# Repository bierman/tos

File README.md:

# TOS Board Connection Map (v1.1)

## Raspberry Pi Connecter
| Raspberry Pi Physical Pin   | GPIO Pin              | TOS Connection                                                | Description             |
|-----------------------------|-----------------------|---------------------------------------------------------------|-------------------------|
| 1                           | 3.3v                  | 3.3v line (jumpered with pi pin 1)                            | 3.3v                    |
| 2                           | 5v                    | 5v line (jumpered with pin 4)                                 | 5v                      |
| 3                           | GPIO 2 / SDA1         | Red LED through R1 (330 Ohm)                                  | LED Red                 |
| 4                           | 5v                    | 5v line (jumpered with pin 2)                                 | 5v                      |
| 5                           | GPIO 3 / SCL1         | NC                                                            | NC                      |
| 6                           | GND                   | GND (all grounds jumpered)                                    | Ground                  |
| 7                           | GPIO 4                | NC                                                            | NC                      |
| 8                           | GPIO 14 / TXD         | MAX232 Pin 11                                                 | TX TTL                  |
| 9                           | GND                   | GND (all grounds jumpered)                                    | Ground                  |
| 10                          | GPIO 15 / RXD         | MAX232 Pin 12                                                 | RX TTL                  |
| 11                          | GPIO 17               | Blue LED through R3 (220 Ohm)                                 | LED Blue                |
| 12                          | GPIO 18               | NC                                                            | NC                      |
| 13                          | GPIO 27               | Green LED through R2 (220 Ohm)                                | LED Green               |
| 14                          | GND                   | GND (all grounds jumpered)                                    | Ground                  |
| 15                          | GPIO 22               | SW1 - Pull up to 3.3v through R6 (4.7K Ohm)                   | Button                  |
| 16                          | GPIO 23               | Keyboard pin 5                                                | PS2 Keyboard CLK        |
| 17                          | 3.3v                  | 3.3v line (jumpered with pi pin 17)                           | 3.3v                    |
| 18                          | GPIO 24               | Keyboard Pin 1                                                | PS2 Keyboard Data       |
| 19                          | GPIO 10 / MOSI        | PMOD pin 2                                                    | PMOD 2 MOSI             |
| 20                          | GND                   | GND (all grounds jumpered)                                    | Ground                  |
| 21                          | GPIO 9 / MISO         | PMOD pin 3                                                    | PMOD 3 MISO             |
| 22                          | GPIO 25               | NC                                                            | NC                      |
| 23                          | GPIO 11 / SCLK        | PMOD pin 4                                                    | PMOD 4 SCK              |
| 24                          | GPIO 8 / CE0          | PMOD pin 1                                                    | PMOD 1 CS               |
| 25                          | GND                   | GND (all grounds jumpered)                                    | Ground                  |
| 26                          | GPIO 7 / CE1          | NC                                                            | NC                      |
| 27                          | GPIO 0 / ID_SD (SDA0) | Mouse Pin 1                                                   | PS2 Mouse Data          |
| 28                          | GPIO 1 / ID_SC (SCL0) | Mouse Pin 5                                                   | PS2 Mouse CLK           |
| 29                          | GPIO 5                | NC                                                            | NC                      |
| 30                          | GND                   | GND (all grounds jumpered)                                    | Ground                  |
| 31                          | GPIO 6                | NC                                                            | NC                      |
| 32                          | GPIO 12 / PWM0        | PMOD pin 7                                                    | PMOD7 - Int             |
| 33                          | GPIO 13 / PWM1        | NC                                                            | NC                      |
| 34                          | GND                   | GND (all grounds jumpered)                                    | Ground                  |
| 35                          | GPIO 19               | NC                                                            | NC                      |
| 36                          | GPIO 16               | PDOD pin 8                                                    | PMOD8 - Reset           |
| 37                          | GPIO 26               | NC                                                            | NC                      |
| 38                          | GPIO 20 / PCM_DIN     | PMOD pin 9                                                    | PMOD9                   |
| 39                          | GND                   | GND (all grounds jumpered)                                    | Ground                  |
| 40                          | GPIO 21 / PCM_DOUT    | PMOD pin 10                                                   | PMOD10                  |

## RS-232 Connecter

| RS-232 Connector            | GPIO Pin              | TOS Connection                                                | Description             |
|-----------------------------|-----------------------|---------------------------------------------------------------|-------------------------|
| 1                           |                       | NC                                                            | NC                      |
| 2                           |                       | MAX232 Pin 13                                                 | RX                      |
| 3                           |                       | MAX232 Pin 14                                                 | TX                      |
| 4                           |                       | NC                                                            | NC                      |
| 5                           |                       | GND                                                           | Ground                  |
| 6                           |                       | NC                                                            | NC                      |
| 7                           |                       | Jumpered to RS232 Pin 8                                       | Jumpered to RS232 Pin 8 |
| 8                           |                       | Jumpered to RS232 Pin 7                                       | Jumpered to RS232 Pin 7 |
| 9                           |                       | NC                                                            | NC                      |

## MAX232 chip

| MAX232                      | GPIO Pin              | TOS Connection                                                | Description             |
|-----------------------------|-----------------------|---------------------------------------------------------------|-------------------------|
| 1                           |                       | C1+ (0.1uf) to MAX232 pin 3                                   |                         |
| 2                           |                       | C4+ (0.1uf) to GND                                            |                         |
| 3                           |                       | C1- (0.1uf) to MAX232 pin 1                                   |                         |
| 4                           |                       | C2+ (0.1uf) to MAX232 pin 5                                   |                         |
| 5                           |                       | C2- (0.1uf) to MAX232 pin 4                                   |                         |
| 6                           |                       | C3- (0.1uf) to GND                                            |                         |
| 7                           |                       | NC                                                            | NC                      |
| 8                           |                       | NC                                                            | NC                      |
| 9                           |                       | NC                                                            | NC                      |
| 10                          |                       | GND                                                           | Ground                  |
| 11                          |                       | PI Physical pin 8                                             | TXTTL                   |
| 12                          |                       | Pi Physical Pin 10                                            | RXTTL                   |
| 13                          |                       | RS232 Pin 2                                                   | RX                      |
| 14                          |                       | RS232 Pin 3                                                   | TX                      |
| 15                          |                       | GND                                                           | Ground                  |
| 16                          |                       | 3.3v                                                          | 3.3v                    |

## PMOD Connecter

| PMOD                        | GPIO Pin              | TOS Connection                                                | Description             |
|-----------------------------|-----------------------|---------------------------------------------------------------|-------------------------|
| 1                           | GPIO 8 / CE0          | Pi Physical Pin 24                                            | PMOD 1 - CS             |
| 2                           | GPIO 10 / MOSI        | Pi Physical Pin 19                                            | PMOD 2 - MOSI           |
| 3                           | GPIO 9 / MISO         | Pi Physical Pin 21                                            | PMOD 3  - MISO          |
| 4                           | GPIO 11 / SCLK        | Pi Physical Pin 23                                            | PMOD 4 - SClock         |
| 5                           |                       | GND                                                           | Ground                  |
| 6                           |                       | 3.3v                                                          | 3.3v                    |
| 7                           | GPIO 12 / PWM0        | Pi Physical Pin 32                                            | PMOD 7 - INT            |
| 8                           | GPIO 16               | Pi Physical Pin 36                                            | PMOD 8 - RESET          |
| 9                           | GPIO 20 / PCM_DIN     | Pi Physical Pin 38                                            | PMOD 9                  |
| 10                          | GPIO 21 / PCM_DOUT    | Pi Physical Pin 40                                            | PMOD 10                 |
| 11                          |                       | GND                                                           | Ground                  |
| 12                          |                       | 3.3v                                                          | 3.3v                    |

## PS2 Mouse Connecter

| PS2 Mouse                   | GPIO Pin              | TOS Connection                                                | Description             |
|-----------------------------|-----------------------|---------------------------------------------------------------|-------------------------|
| 1                           | GPIO 0 / ID_SD (SDA0) | Pi Physical Pin 27 (pull up to 3.3v through R8 (2K Ohm)       | PS2 Mouse Data          |
| 2                           |                       | NC                                                            | NC                      |
| 3                           |                       | GND                                                           | Ground                  |
| 4                           |                       | 5v                                                            | 5v                      |
| 5                           | GPIO 1 / ID_SC (SCL0) | Pi Physical Pin 28 (pull up to 3.3v through R7 (2K Ohm)       | PS2 Mouse Clock         |
| 6                           |                       | NC                                                            | NC                      |

## PS2 Keyboard Connecter

| PS2 Keyboard                | GPIO Pin              | TOS Connection                                                | Description             |
|-----------------------------|-----------------------|---------------------------------------------------------------|-------------------------|
| 1                           | GPIO 24               | Pi Physical Pin 18 (pull up to 3.3v through R5 (2K Ohm)       | PS2 Keyboard Data       |
| 2                           |                       | NC                                                            | NC                      |
| 3                           |                       | GND                                                           | Ground                  |
| 4                           |                       | 5v                                                            | 5v                      |
| 5                           | GPIO 23               | Pi Physical Pin 16 (pull up to 3.3v through R4 (2K Ohm)       | PS2 Keyboard Clock      |
| 6                           |                       | NC                                                            | NC                      |

## Breakout Connecter

| Breakout                    | GPIO Pin              | TOS Connection                                                | Description             |
|-----------------------------|-----------------------|---------------------------------------------------------------|-------------------------|
| 1                           |                       | GND                                                           | Ground                  |
| 2                           | GPIO 22               | Pi Physical 15  / SW1 - Pull up to 3.3v through R6 (4.7K Ohm) | Button                  |
| 3                           | GPIO 2 / SDA1         | Pi Physical Pin 3                                             | Red LED                 |
| 4                           | GPIO 24               | Pi Physical Pin 18 / PS2 Keyboard pin 1                       | PS2 Keyboar Data        |
| 5                           | GPIO 23               | Pi Physical Pin 16 / PS2 Keyboard pin 5                       | PS2 Keyboard Clock      |
| 6                           |                       | RS-232 pin 4                                                  | RX                      |
| 7                           |                       | RS-232 pin 3                                                  | TX                      |

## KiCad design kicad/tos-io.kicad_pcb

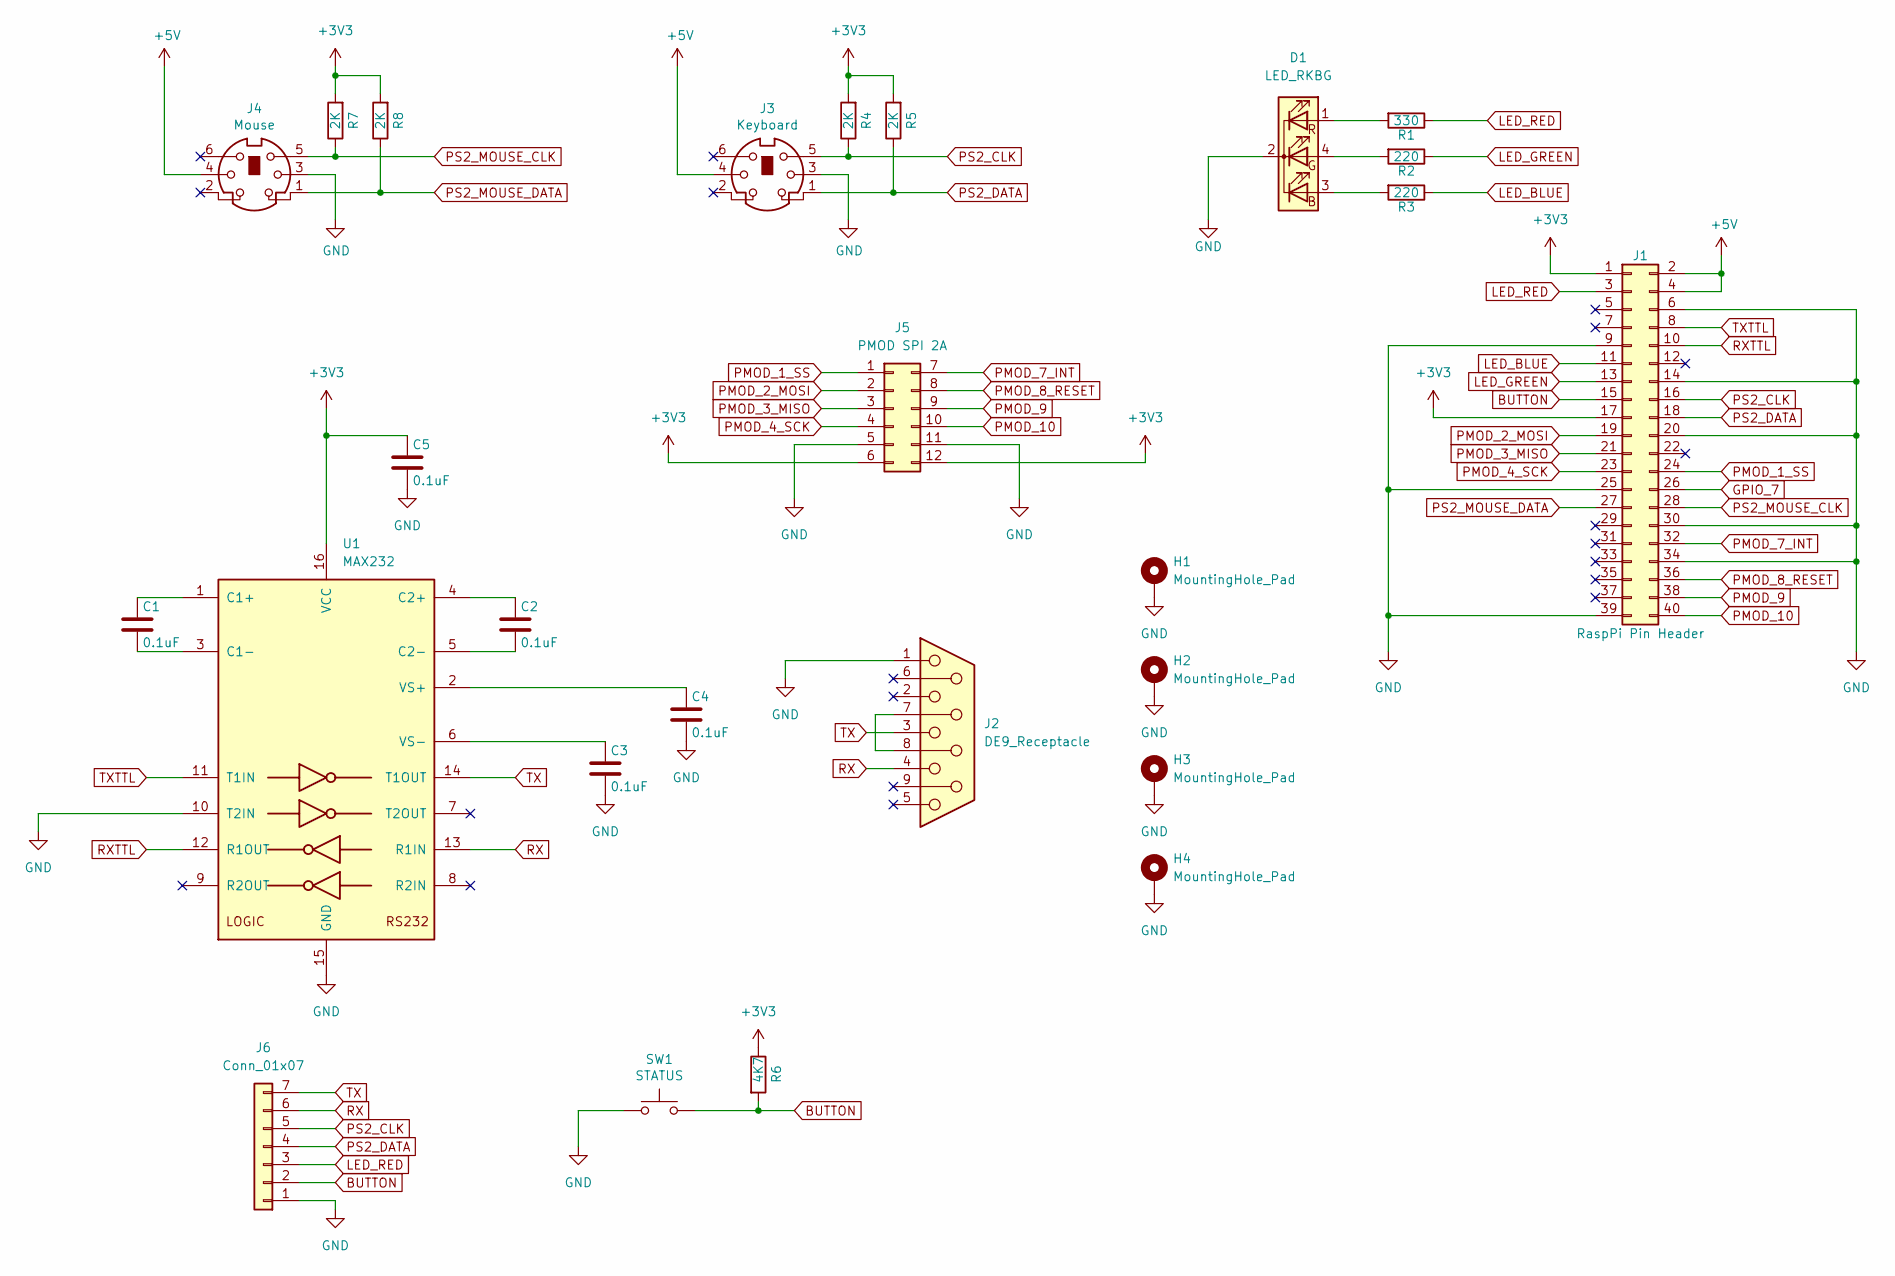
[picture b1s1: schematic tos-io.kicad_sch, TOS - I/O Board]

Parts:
C1, C2, C3, C4, C5: 0.1uF; C_0805_2012Metric_Pad1.18x1.45mm_HandSolder; LCSC C49678
D1: LED_RKBG; LED_D5.0mm-4_RGB
H1, H2, H3, H4: MountingHole_Pad; MountingHole_3mm_Pad_Via
J1: RaspPi Pin Header; PinHeader_2x20_P2.54mm_Vertical; LCSC C132439
J2: DE9_Receptacle; DSUB-9_Female_Horizontal_P2.77x2.84mm_EdgePinOffset7.70mm_H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
J3: Keyboard; minidin_6_ps2_pcb_mount; LCSC C77848
J4: Mouse; minidin_6_ps2_pcb_mount
J5: PMOD SPI 2A; PinSocket_2x06_Top_Bottom_P2.54mm_Vertical; LCSC C358728
J6: Conn_01x07; PinHeader_1x07_P2.54mm_Vertical; LCSC C5360900
R1: 330; R_0805_2012Metric_Pad1.20x1.40mm_HandSolder
R2, R3: 220; R_0805_2012Metric_Pad1.20x1.40mm_HandSolder
R4, R5, R7, R8: 2K; R_0805_2012Metric_Pad1.20x1.40mm_HandSolder
R6: 4K7; R_0805_2012Metric_Pad1.20x1.40mm_HandSolder
SW1: STATUS; SW_PUSH_6mm; LCSC C722960
U1: MAX232; TSSOP-16_4.4x5mm_P0.65mm; LCSC C406863

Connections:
+3V3: C5.1, J1.1, J1.17, J5.6, J5.12, R4.2, R5.2, R6.1, R7.2, R8.2, U1.16 (VCC)
+5V: J1.2, J1.4, J3.4, J4.4
BUTTON: J1.15, J6.2, R6.2, SW1.2
GND: C3.2, C4.2, C5.2, D1.2 (K), H1.1, H2.1, H3.1, H4.1, J1.6, J1.9, J1.14, J1.20, J1.25, J1.30, J1.34, J1.39, J2.1, J3.3, J4.3, J5.5, J5.11, J6.1, SW1.1, U1.10 (T2IN), U1.15 (GND)
GPIO_7: J1.26
LED_BLUE: J1.11, R3.1
LED_GREEN: J1.13, R2.1
LED_RED: J1.3, J6.3, R1.1
unnamed: D1.3 (BA), R3.2
unnamed: D1.4 (GA), R2.2
unnamed: D1.1 (RA), R1.2
unnamed: J2.7, J2.8
unnamed: C1.1, U1.1 (C1+)
unnamed: C1.2, U1.3 (C1-)
unnamed: C2.1, U1.4 (C2+)
unnamed: C2.2, U1.5 (C2-)
unnamed: C4.1, U1.2 (VS+)
unnamed: C3.1, U1.6 (VS-)
PMOD_1_SS: J1.24, J5.1
PMOD_2_MOSI: J1.19, J5.2
PMOD_3_MISO: J1.21, J5.3
PMOD_4_SCK: J1.23, J5.4
PMOD_7_INT: J1.32, J5.7
PMOD_8_RESET: J1.36, J5.8
PMOD_9: J1.38, J5.9
PMOD_10: J1.40, J5.10
PS2_CLK: J1.16, J3.5, J6.5, R4.1
PS2_DATA: J1.18, J3.1, J6.4, R5.1
PS2_MOUSE_CLK: J1.28, J4.5, R7.1
PS2_MOUSE_DATA: J1.27, J4.1, R8.1
RX: J2.4, J6.6, U1.13 (R1IN)
RXTTL: J1.10, U1.12 (R1OUT)
TX: J2.3, J6.7, U1.14 (T1OUT)
TXTTL: J1.8, U1.11 (T1IN)

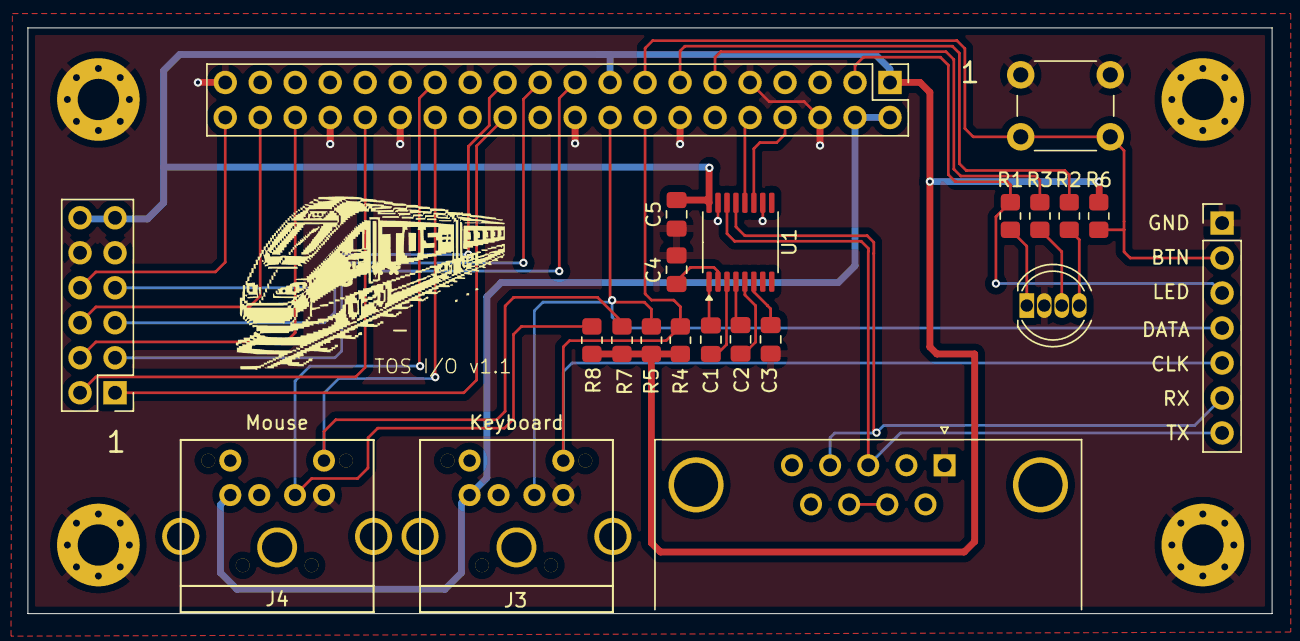
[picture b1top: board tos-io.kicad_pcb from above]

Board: 2 copper layers, 90.3 x 42.5 mm, 26 parts (0 on the bottom side), 33 nets.

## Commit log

2025-02-06 TOS I/O KiCad schematics
2025-03-02 Blink example for raspi-os
2025-03-02 Button example for raspi-os using MMIO
2025-03-02 LED matrix example for raspi-os
2025-09-04 Add breakout header on TOS I/O board
2025-09-19 Update README with TOS Board Connection Map
